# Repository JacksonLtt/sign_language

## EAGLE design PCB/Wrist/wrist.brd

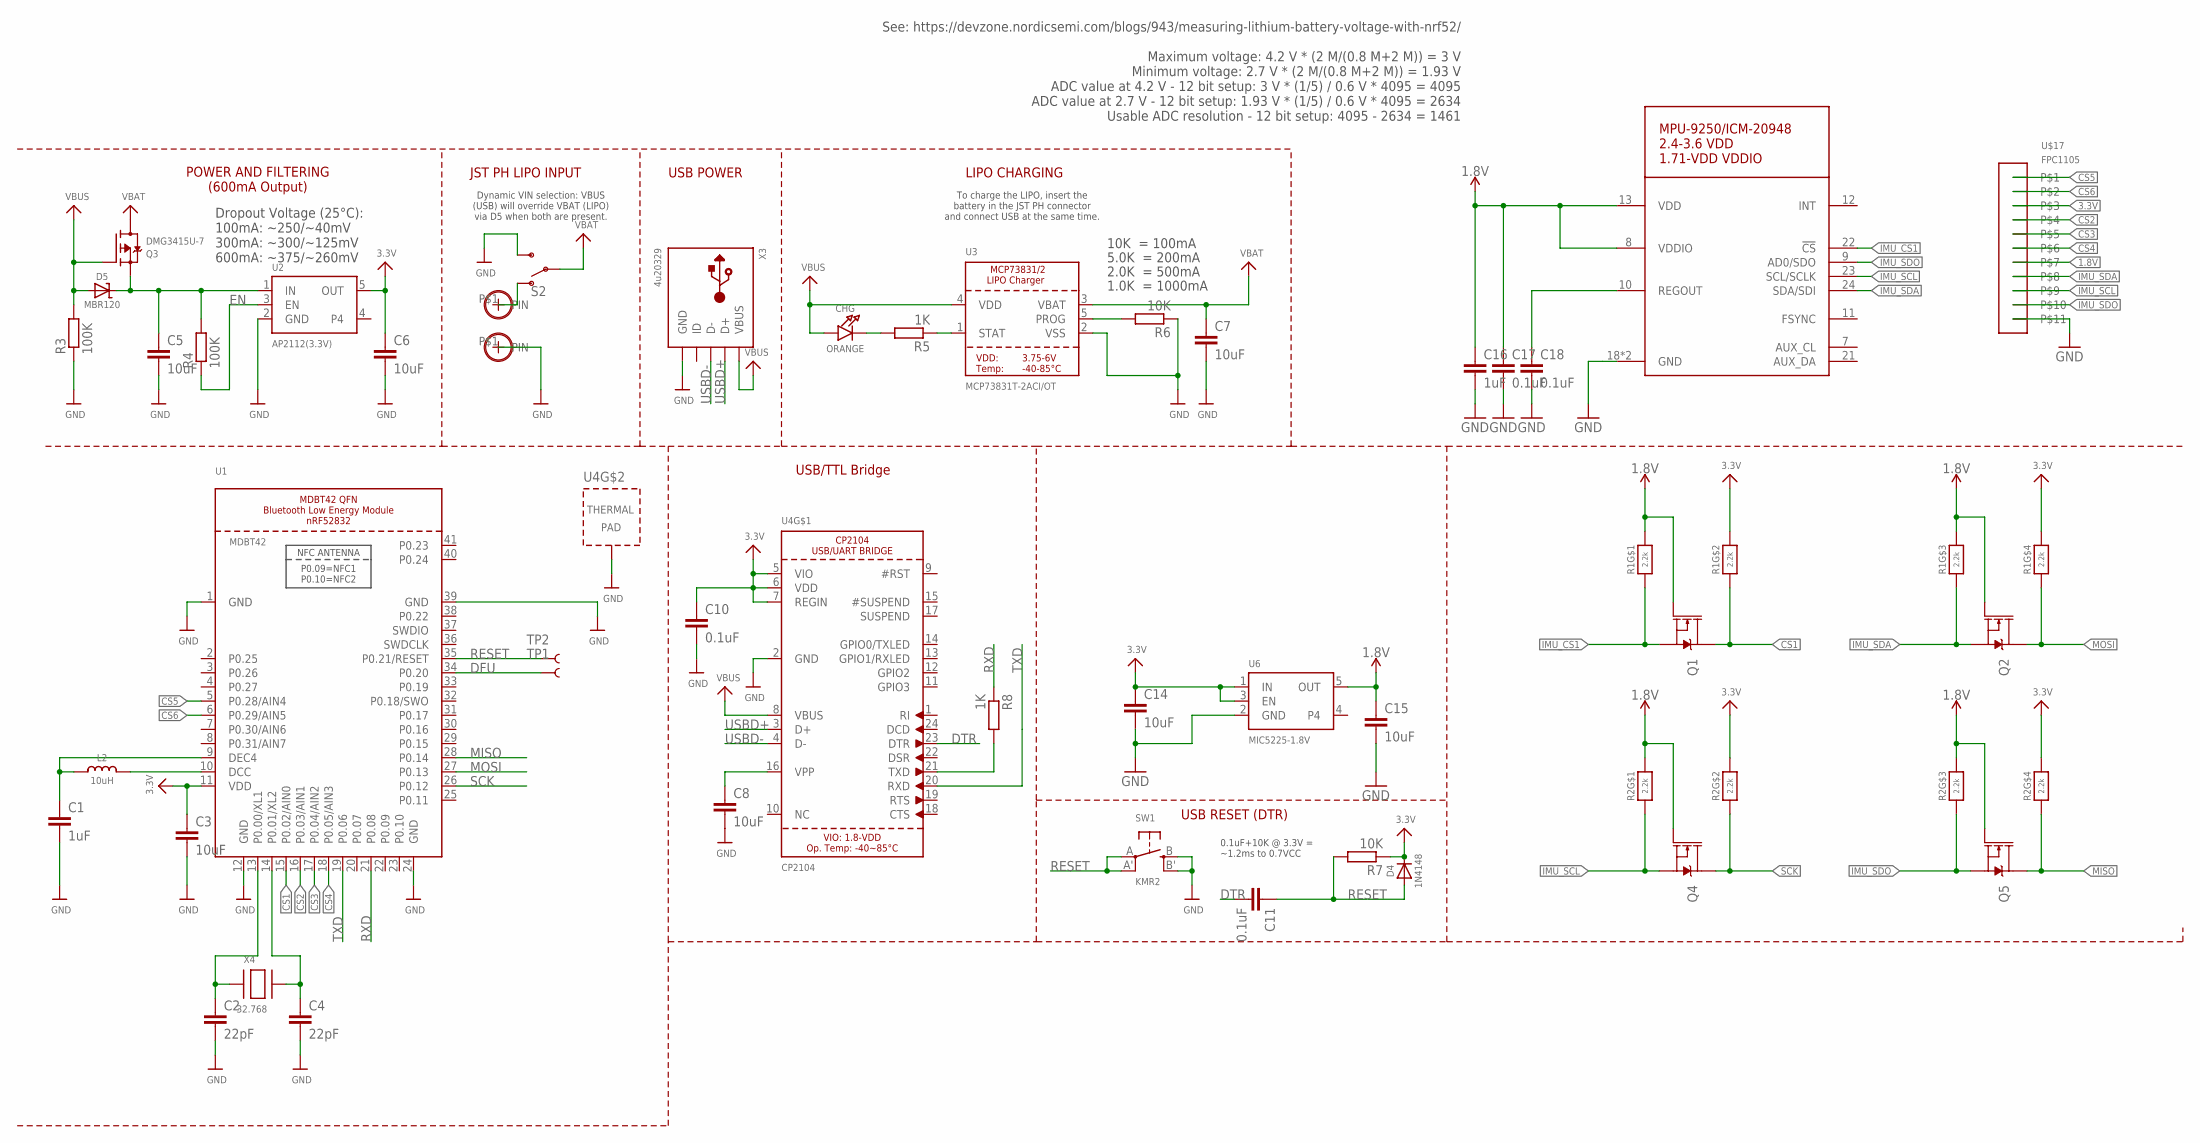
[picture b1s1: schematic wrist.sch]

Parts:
C1, C16: 1uF; SPARKFUN-CAPACITORS_0402
C2, C4: 22pF; SPARKFUN-CAPACITORS_0402
C3, C5, C6, C7, C8, C14, C15: 10uF; SPARKFUN-CAPACITORS_0402
C10, C11, C17, C18: 0.1uF; SPARKFUN-CAPACITORS_0402
CHG: ORANGE; CHIPLED_0805_NOOUTLINE
D4: 1N4148; SOD-323
D5: MBR120; SOD-123
IC1: ADAFRUIT_SENSOR_MPU-9250_ICM20948; ADAFRUIT_SENSOR_QFN24_3MM_NOEP
L2: 10uH; 0805-NO
Q1, Q2, Q4, Q5: 20V/0.2A/8MHz/1.2Ω/1Vth; SPARKFUN-DISCRETESEMI_SOT-416FL
Q3: DMG3415U-7; SOT23-R
R1, R2: 2.2k; MICROBUILDER_RESPACK_4X0603
R3, R4: 100K; R0603
R5, R8: 1K; R0603
R6, R7: 10K; R0603
S2: SWITCH-SPDT-SMD-RIGHT-ANGLE; SWITCH_SPST_SMD_A
SW1: KMR2; BTN_KMR2_4.6X2.8
TP1, TP2: TEST-POINT3; PAD.03X.03
U1: MDBT42; BLE_MODULE_RAYTAC_MDBT42
U2: AP2112(3.3V); SOT23-5
U3: MCP73831T-2ACI/OT; SOT23-5
U4: CP2104; QFN24_4MM_SMSC
U6: MIC5225-1.8V; MICROBUILDER_SOT23-5
U$17: FPC1105
U$23, U$28: M3-HOLE_M0.9-HOLE0.9MM; M3-HOLE_M0.9-HOLE
X3: 4u20329; 4UCONN_20329_V2
X4: 32.768; XTAL3215

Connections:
1.8V: C15.1, C16.1, C17.1, IC1.8 (VDDIO), IC1.13 (VDD), Q1.1 (G), Q2.1 (G), Q4.1 (G), Q5.1 (G), R1.6 (2), R1.8 (2), R2.6 (2), R2.8 (2), U6.5 (OUT), U$17.P$7
3.3V: C3.1, C6.1, C10.1, C14.1, D4.C, R1.5 (2), R1.7 (2), R2.5 (2), R2.7 (2), R7.1, U1.11 (VDD), U2.5 (OUT), U4.5 (VIO), U4.6 (VDD), U4.7 (REGIN), U6.1 (IN), U6.3 (EN), U$17.P$3
CS1: Q1.3 (D), R1.2 (1), U1.15 (P0.02/AIN0)
CS2: U1.16 (P0.03/AIN1), U$17.P$4
CS3: U1.17 (P0.04/AIN2), U$17.P$5
CS4: U1.18 (P0.05/AIN3), U$17.P$6
CS5: U1.5 (P0.28/AIN4), U$17.P$1
CS6: U1.6 (P0.29/AIN5), U$17.P$2
DFU: TP1.P$1, U1.34 (P0.20)
DTR: C11.2, U4.23 (DTR)
EN: R4.1, U2.3 (EN)
GND: C1.2, C2.2, C3.2, C4.2, C5.2, C6.2, C7.2, C8.2, C10.2, C14.2, C15.2, C16.2, C17.2, C18.2, IC1.18 (GND), IC1.20 (GND), R3.1, R6.1, S2.3 (S), SW1.B (S), SW1.B' (S1), U1.1 (GND), U1.12 (GND), U1.24 (GND), U1.39 (GND), U2.2 (GND), U3.2 (VSS), U4.2 (GND), U4.THERM (TP), U6.2 (GND), U$17.P$11, U$28.P$1, X3.BASE@1 (GND), X3.BASE@2 (GND), X3.GND, X3.SPRT@1 (GND), X3.SPRT@2 (GND), X3.SPRT@3 (GND), X3.SPRT@4 (GND)
IMU_CS1: IC1.22 (!CS), Q1.2 (S), R1.1
IMU_SCL: IC1.23 (SCL/SCLK), Q4.2 (S), R2.1, U$17.P$9
IMU_SDA: IC1.24 (SDA/SDI), Q2.2 (S), R1.3 (1), U$17.P$8
IMU_SDO: IC1.9 (AD0/SDO), Q5.2 (S), R2.3 (1), U$17.P$10
MISO: Q5.3 (D), R2.4 (1), U1.28 (P0.14)
MOSI: Q2.3 (D), R1.4 (1), U1.27 (P0.13)
unnamed: C2.1, U1.13 (P0.00/XL1), X4.P$1
unnamed: C4.1, U1.14 (P0.01/XL2), X4.P$2
unnamed: L2.2, U1.10 (DCC)
unnamed: CHG.C, R5.2
unnamed: S2.1 (O), U$23.P$1
unnamed: C18.1, IC1.10 (REGOUT)
unnamed: C1.1, L2.1, U1.9 (DEC4)
unnamed: R5.1, U3.1 (STAT)
unnamed: R6.2, U3.5 (PROG)
unnamed: R8.2, U4.21 (TXD)
unnamed: C8.1, U4.16 (VPP)
RESET: C11.1, D4.A, R7.2, SW1.A, SW1.A' (P1), TP2.P$1, U1.35 (P0.21/RESET)
RXD: R8.1, U1.21 (P0.08)
SCK: Q4.3 (D), R2.2 (1), U1.26 (P0.12)
TXD: U1.19 (P0.06), U4.20 (RXD)
USBD+: U4.3 (D+), X3.D+
USBD-: U4.4 (D-), X3.D-
VBAT: C7.1, Q3.3 (D), S2.2, U3.3 (VBAT)
VBUS: CHG.A, D5.A, Q3.1 (G), R3.2, U3.4 (VDD), U4.8 (VBUS), X3.VBUS
VIN: C5.1, D5.C, Q3.2 (S), R4.2, U2.1 (IN)

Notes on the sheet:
10K = 100mA
5.0K = 200mA
2.0K = 500mA
1.0K = 1000mA
LIPO CHARGING
To charge the LIPO, insert the battery in the JST PH connector and connect USB at the same time.
POWER AND FILTERING (600mA Output)
JST PH LIPO INPUT
Dynamic VIN selection: VBUS (USB) will override VBAT (LIPO) via D5 when both are present.
Dropout Voltage (25°C): 100mA: ~250/~40mV 300mA: ~300/~125mV 600mA: ~375/~260mV
USB POWER
USB/TTL Bridge
See: https://devzone.nordicsemi.com/blogs/943/measuring-lithium-battery-voltage-with-nrf52/ Maximum voltage: 4.2 V * (2 M/(0.8 M+2 M)) = 3 V Minimum voltage: 2.7 V * (2 M/(0.8 M+2 M)) = 1.93 V ADC value at 4.2 V - 12 bit setup: 3 V * (1/5) / 0.6 V * 4095 = 4095 ADC value at 2.7 V - 12 bit setup: 1.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
USB RESET (DTR)
0.1uF+10K @ 3.3V = ~1.2ms to 0.7VCC

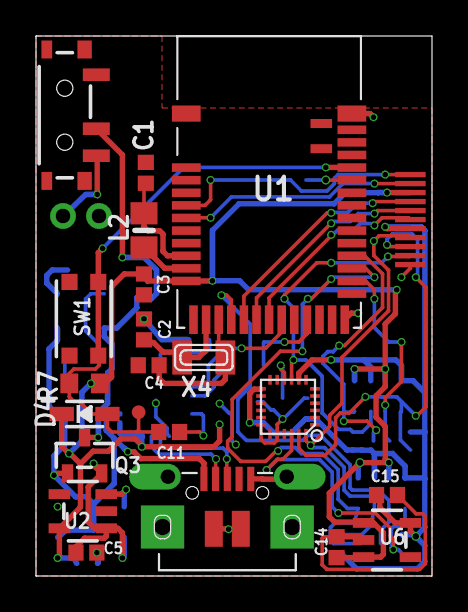
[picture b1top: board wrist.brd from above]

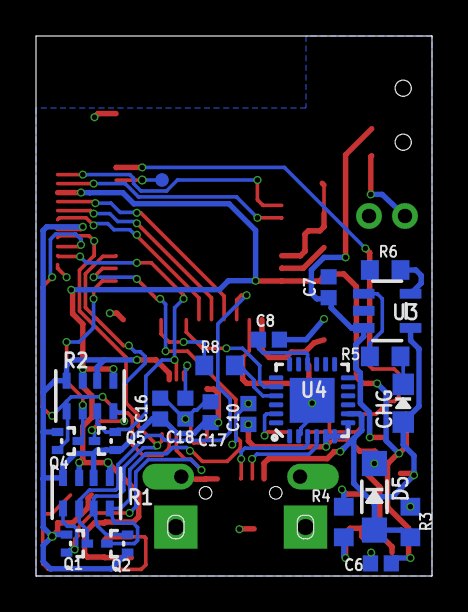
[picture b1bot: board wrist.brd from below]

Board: 2 copper layers, 22.0 x 30.0 mm, 47 parts (23 on the bottom side), 38 nets.

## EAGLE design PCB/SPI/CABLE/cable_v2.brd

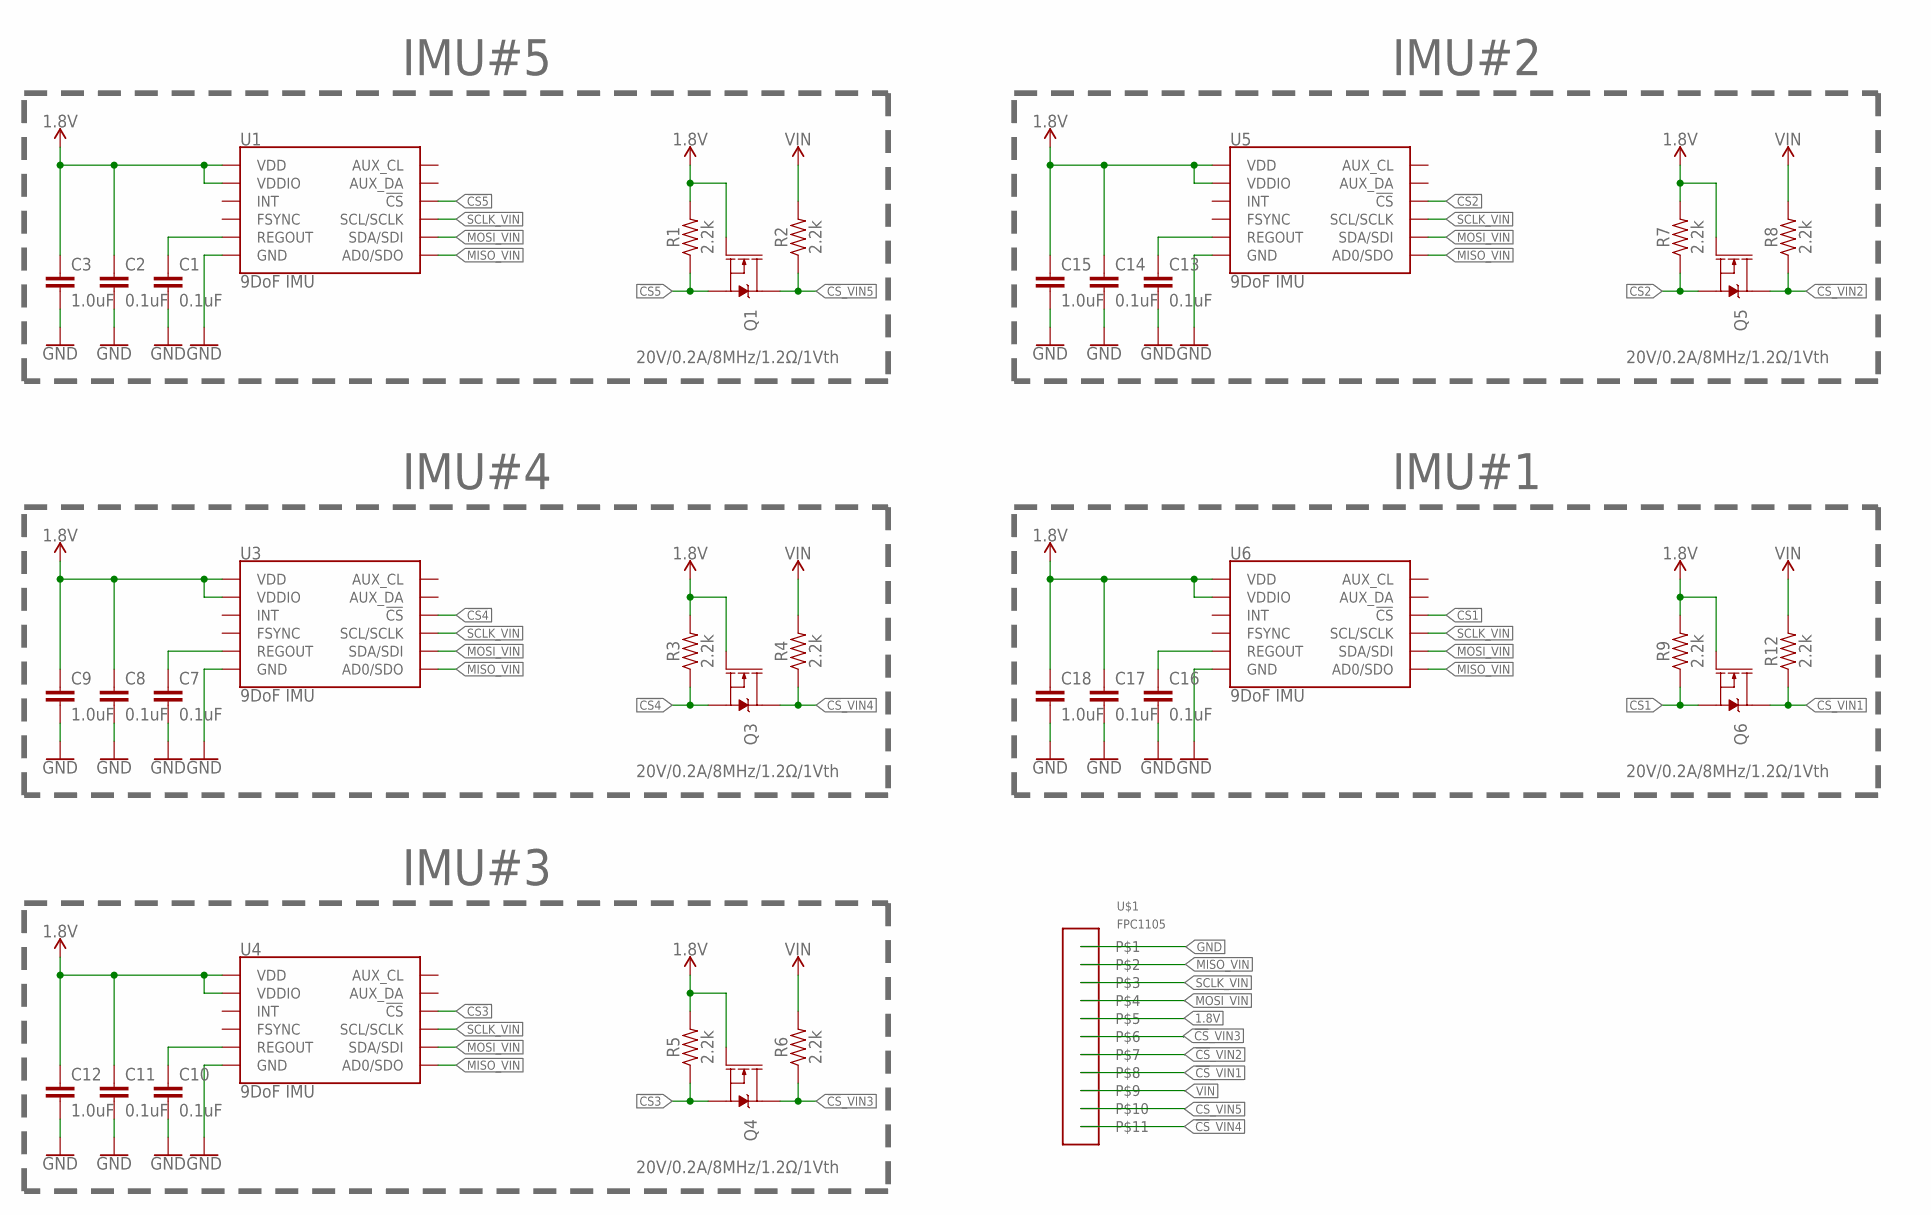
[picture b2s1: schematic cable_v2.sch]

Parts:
C1, C2, C7, C8, C10, C11, C13, C14, C16, C17: 0.1uF; C0402
C3, C9, C12, C15, C18: 1.0uF; C0402
Q1, Q3, Q4, Q5, Q6: 20V/0.2A/8MHz/1.2Ω/1Vth; SOT-416FL
R1, R2, R3, R4, R5, R6, R7, R8, R9, R12: 2.2k; 0402-TIGHT
U1, U3, U4, U5, U6: 9DoF IMU; QFN24-3X3
U$1: FPC1105

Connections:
1.8V: C2.1, C3.1, C8.1, C9.1, C11.1, C12.1, C14.1, C15.1, C17.1, C18.1, Q1.1 (G), Q3.1 (G), Q4.1 (G), Q5.1 (G), Q6.1 (G), R1.2, R3.2, R5.2, R7.2, R9.2, U1.8 (VDDIO), U1.13 (VDD), U3.8 (VDDIO), U3.13 (VDD), U4.8 (VDDIO), U4.13 (VDD), U5.8 (VDDIO), U5.13 (VDD), U6.8 (VDDIO), U6.13 (VDD), U$1.P$5
!CS1: Q6.2 (S), R9.1, U6.22 (!CS)
!CS2: Q5.2 (S), R7.1, U5.22 (!CS)
!CS3: Q4.2 (S), R5.1, U4.22 (!CS)
!CS4: Q3.2 (S), R3.1, U3.22 (!CS)
!CS5: Q1.2 (S), R1.1, U1.22 (!CS)
!CS!_VIN1: Q6.3 (D), R12.1, U$1.P$8
!CS!_VIN2: Q5.3 (D), R8.1, U$1.P$7
!CS!_VIN3: Q4.3 (D), R6.1, U$1.P$6
!CS!_VIN4: Q3.3 (D), R4.1, U$1.P$11
!CS!_VIN5: Q1.3 (D), R2.1, U$1.P$10
GND: C1.2, C2.2, C3.2, C7.2, C8.2, C9.2, C10.2, C11.2, C12.2, C13.2, C14.2, C15.2, C16.2, C17.2, C18.2, U1.18 (GND), U1.20 (GND), U3.18 (GND), U3.20 (GND), U4.18 (GND), U4.20 (GND), U5.18 (GND), U5.20 (GND), U6.18 (GND), U6.20 (GND), U$1.P$1
MISO_VIN: U1.9 (AD0/SDO), U3.9 (AD0/SDO), U4.9 (AD0/SDO), U5.9 (AD0/SDO), U6.9 (AD0/SDO), U$1.P$2
MOSI_VIN: U1.24 (SDA/SDI), U3.24 (SDA/SDI), U4.24 (SDA/SDI), U5.24 (SDA/SDI), U6.24 (SDA/SDI), U$1.P$4
unnamed: C1.1, U1.10 (REGOUT)
unnamed: C7.1, U3.10 (REGOUT)
unnamed: C10.1, U4.10 (REGOUT)
unnamed: C13.1, U5.10 (REGOUT)
unnamed: C16.1, U6.10 (REGOUT)
SCLK_VIN: U1.23 (SCL/SCLK), U3.23 (SCL/SCLK), U4.23 (SCL/SCLK), U5.23 (SCL/SCLK), U6.23 (SCL/SCLK), U$1.P$3
VIN: R2.2, R4.2, R6.2, R8.2, R12.2, U$1.P$9

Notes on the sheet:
IMU#5
IMU#4
IMU#3
IMU#2
IMU#1

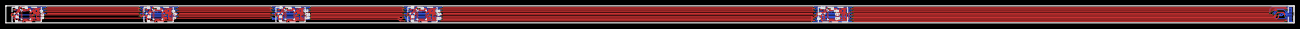
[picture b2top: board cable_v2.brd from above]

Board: 2 copper layers, 439.4 x 5.8 mm, 36 parts (1 on the bottom side), 21 nets.

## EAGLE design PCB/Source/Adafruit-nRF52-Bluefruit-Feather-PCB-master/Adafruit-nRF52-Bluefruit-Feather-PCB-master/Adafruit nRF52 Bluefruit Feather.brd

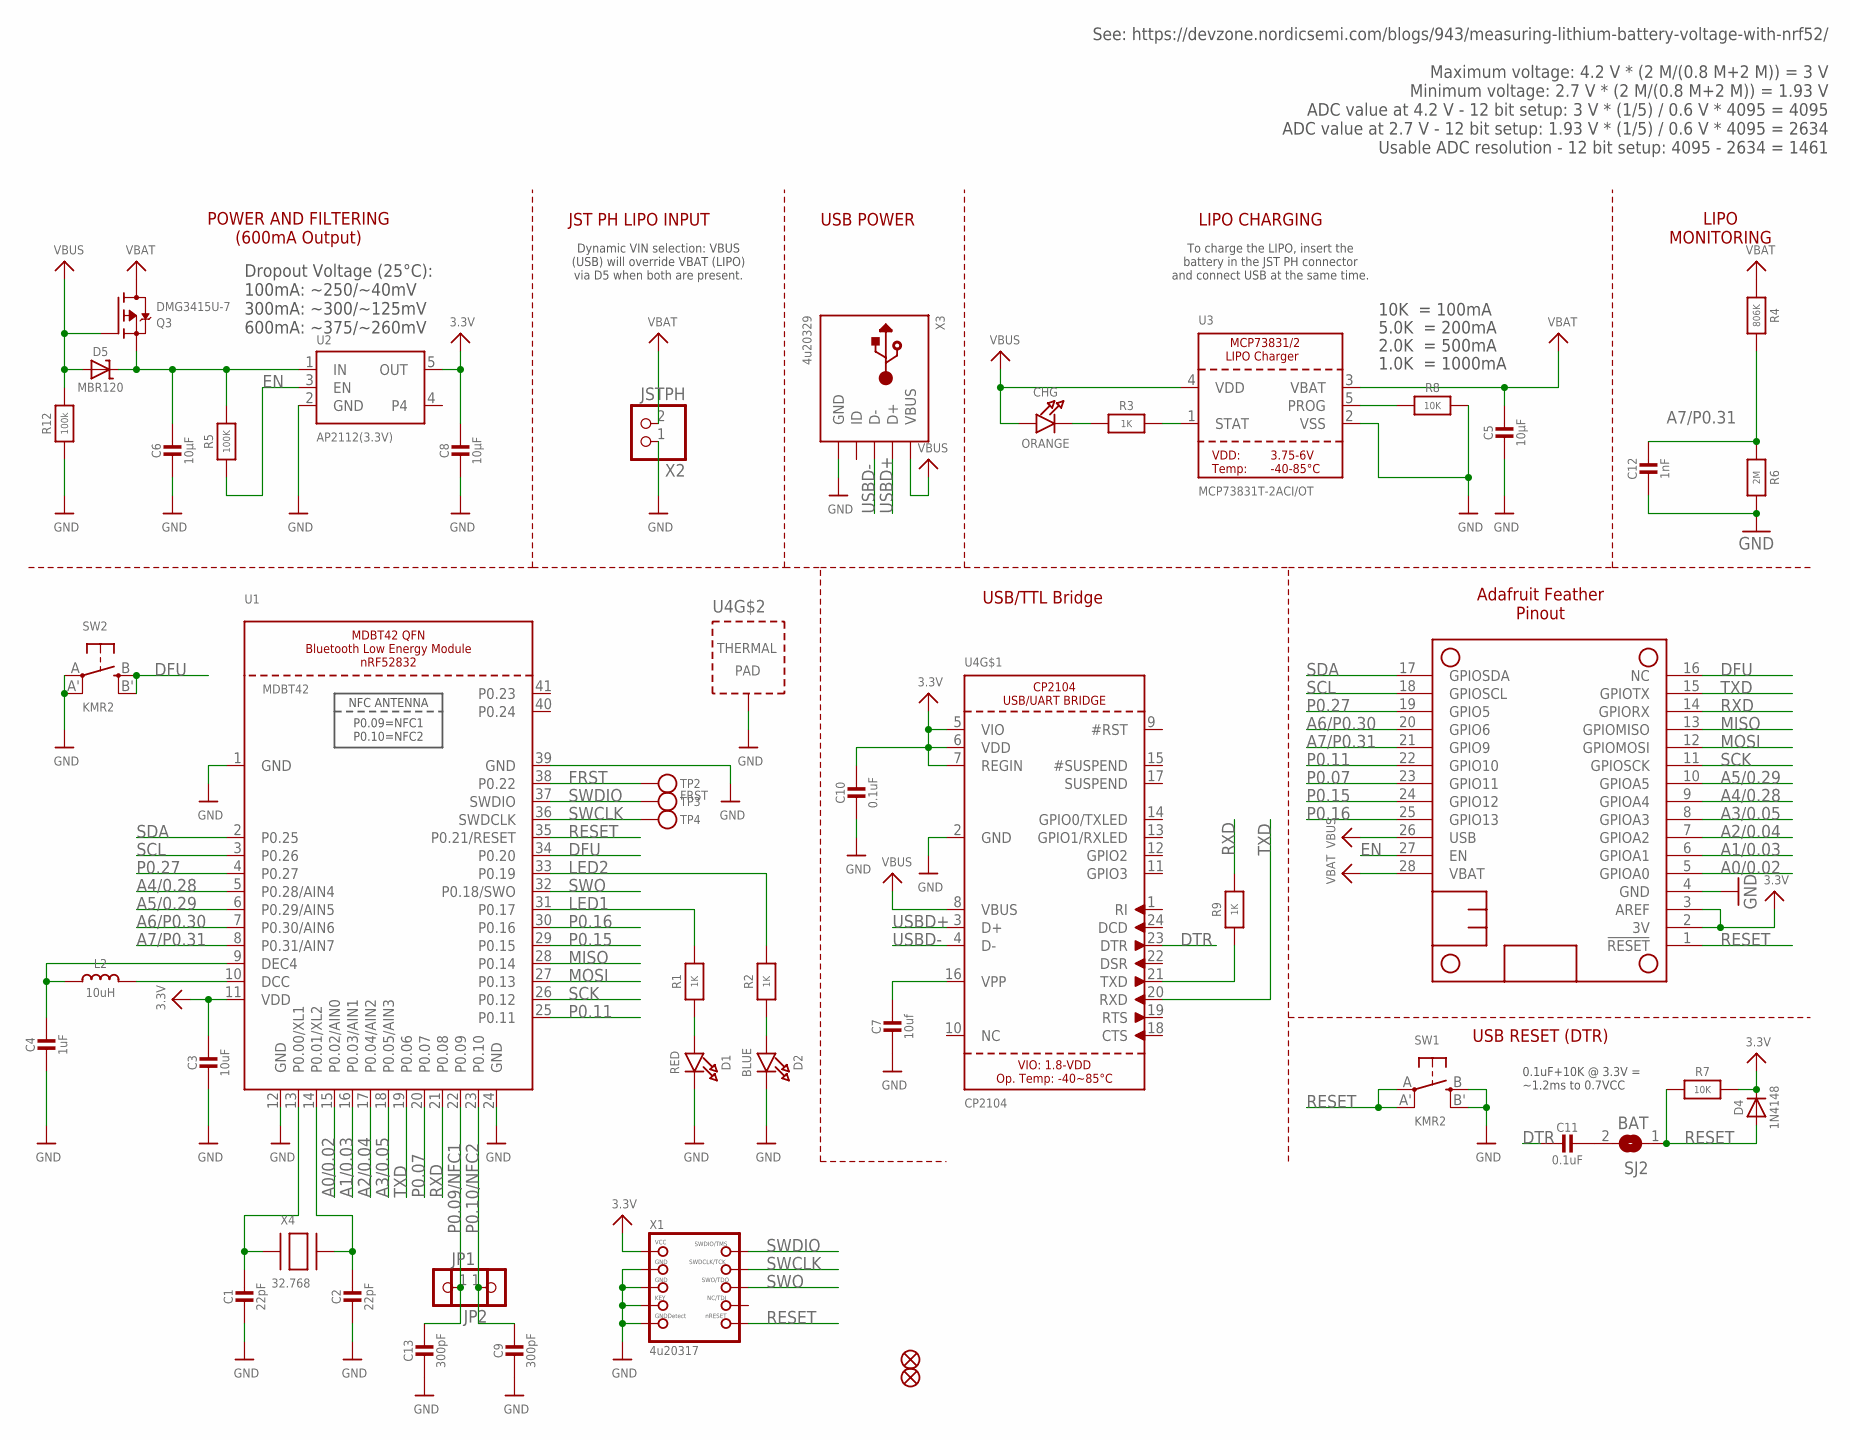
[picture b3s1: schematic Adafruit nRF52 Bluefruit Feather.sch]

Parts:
C1, C2: 22pF; 0603-NO
C3: 10uF; 0805-NO
C4: 1uF; 0603-NO
C5, C6, C8: 10µF; 0805-NO
C7: 10uf; 0805-NO
C9, C13: 300pF; _0603MP
C10, C11: 0.1uF; 0603-NO
C12: 1nF; 0603-NO
CHG: ORANGE; CHIPLED_0805_NOOUTLINE
D1: RED; CHIPLED_0805_NOOUTLINE
D2: BLUE; CHIPLED_0805_NOOUTLINE
D4: 1N4148; SOD-323
D5: MBR120; SOD-123
FID1, FID3: FIDUCIAL_1MM
JP1, JP2: HEADER-1X12MM; 1X01_2MM
L2: 10uH; 0805-NO
MS1: FEATHERWING_NODIM
Q3: DMG3415U-7; SOT23-R
R1, R2, R3, R9: 1K; 0603-NO
R4: 806K; 0603-NO
R5: 100K; 0603-NO
R6: 2M; 0603-NO
R7, R8: 10K; 0603-NO
R12: 100k; 0603-NO
SJ2: BAT; SOLDERJUMPER_CLOSEDWIRE
SW1, SW2: KMR2; BTN_KMR2_4.6X2.8
TP2: FRST; PAD-1.5X2.0
TP3, TP4: TESTPOINTROUND2MM; TESTPOINT_ROUND_2MM
U1: MDBT42; BLE_MODULE_RAYTAC_MDBT42
U2: AP2112(3.3V); SOT23-5
U3: MCP73831T-2ACI/OT; SOT23-5
U4: CP2104; QFN24_4MM_SMSC
X1: 4u20317; 2X05_1.27MM_BOX_POSTS
X2: JSTPH; JSTPH2
X3: 4u20329; 4UCONN_20329_V2
X4: 32.768; XTAL3215

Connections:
3.3V: C3.1, C8.1, C10.1, D4.C, MS1.2 (3V), MS1.3 (AREF), R7.2, U1.11 (VDD), U2.5 (OUT), U4.5 (VIO), U4.6 (VDD), U4.7 (REGIN), X1.1 (VCC)
A0/0.02: MS1.5 (GPIOA0), U1.15 (P0.02/AIN0)
A1/0.03: MS1.6 (GPIOA1), U1.16 (P0.03/AIN1)
A2/0.04: MS1.7 (GPIOA2), U1.17 (P0.04/AIN2)
A3/0.05: MS1.8 (GPIOA3), U1.18 (P0.05/AIN3)
A4/0.28: MS1.9 (GPIOA4), U1.5 (P0.28/AIN4)
A5/0.29: MS1.10 (GPIOA5), U1.6 (P0.29/AIN5)
A6/P0.30: MS1.20 (GPIO6), U1.7 (P0.30/AIN6)
A7/P0.31: C12.1, MS1.21 (GPIO9), R4.2, R6.1, U1.8 (P0.31/AIN7)
DFU: MS1.16 (NC), SW2.B (S), SW2.B' (S1), U1.34 (P0.20)
DTR: C11.2, U4.23 (DTR)
EN: MS1.27 (EN), R5.1, U2.3 (EN)
FRST: TP2.P$1, U1.38 (P0.22)
GND: C1.2, C2.2, C3.2, C4.2, C5.2, C6.2, C7.2, C8.2, C9.2, C10.2, C12.2, C13.2, D1.C, D2.C, MS1.4 (GND), R6.2, R8.2, R12.1, SW1.B (S), SW1.B' (S1), SW2.A, SW2.A' (P1), U1.1 (GND), U1.12 (GND), U1.24 (GND), U1.39 (GND), U2.2 (GND), U3.2 (VSS), U4.2 (GND), U4.THERM (TP), X1.3 (GND), X1.5 (GND), X1.7 (KEY), X1.9 (GNDDETECT), X2.1, X3.BASE@1 (GND), X3.BASE@2 (GND), X3.GND, X3.SPRT@1 (GND), X3.SPRT@2 (GND), X3.SPRT@3 (GND), X3.SPRT@4 (GND)
LED1: R1.2, U1.31 (P0.17)
LED2: R2.2, U1.33 (P0.19)
MISO: MS1.13 (GPIOMISO), U1.28 (P0.14)
MOSI: MS1.12 (GPIOMOSI), U1.27 (P0.13)
unnamed: C1.1, U1.13 (P0.00/XL1), X4.P$1
unnamed: C2.1, U1.14 (P0.01/XL2), X4.P$2
unnamed: L2.2, U1.10 (DCC)
unnamed: CHG.C, R3.1
unnamed: D1.A, R1.1
unnamed: D2.A, R2.1
unnamed: C4.1, L2.1, U1.9 (DEC4)
unnamed: R3.2, U3.1 (STAT)
unnamed: R8.1, U3.5 (PROG)
unnamed: R9.1, U4.21 (TXD)
unnamed: C11.1, SJ2.2
unnamed: C7.1, U4.16 (VPP)
P0.07: MS1.23 (GPIO11), U1.20 (P0.07)
P0.09/NFC1: C13.1, JP2.1, U1.22 (P0.09)
P0.10/NFC2: C9.1, JP1.1, U1.23 (P0.10)
P0.11: MS1.22 (GPIO10), U1.25 (P0.11)
P0.15: MS1.24 (GPIO12), U1.29 (P0.15)
P0.16: MS1.25 (GPIO13), U1.30 (P0.16)
P0.27: MS1.19 (GPIO5), U1.4 (P0.27)
RESET: D4.A, MS1.1 (!RESET), R7.1, SJ2.1, SW1.A, SW1.A' (P1), U1.35 (P0.21/RESET), X1.10 (NRESET)
RXD: MS1.14 (GPIORX), R9.2, U1.21 (P0.08)
SCK: MS1.11 (GPIOSCK), U1.26 (P0.12)
SCL: MS1.18 (GPIOSCL), U1.3 (P0.26)
SDA: MS1.17 (GPIOSDA), U1.2 (P0.25)
SWCLK: TP4.P$1, U1.36 (SWDCLK), X1.4 (SWDCLK)
SWDIO: TP3.P$1, U1.37 (SWDIO), X1.2 (SWDIO)
SWO: U1.32 (P0.18/SWO), X1.6 (SWO)
TXD: MS1.15 (GPIOTX), U1.19 (P0.06), U4.20 (RXD)
USBD+: U4.3 (D+), X3.D+
USBD-: U4.4 (D-), X3.D-
VBAT: C5.1, MS1.28 (VBAT), Q3.3 (D), R4.1, U3.3 (VBAT), X2.2
VBUS: CHG.A, D5.A, MS1.26 (USB), Q3.1 (G), R12.2, U3.4 (VDD), U4.8 (VBUS), X3.VBUS
VIN: C6.1, D5.C, Q3.2 (S), R5.2, U2.1 (IN)

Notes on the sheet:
10K = 100mA
5.0K = 200mA
2.0K = 500mA
1.0K = 1000mA
LIPO CHARGING
LIPO MONITORING
To charge the LIPO, insert the battery in the JST PH connector and connect USB at the same time.
POWER AND FILTERING (600mA Output)
JST PH LIPO INPUT
Dynamic VIN selection: VBUS (USB) will override VBAT (LIPO) via D5 when both are present.
Dropout Voltage (25°C): 100mA: ~250/~40mV 300mA: ~300/~125mV 600mA: ~375/~260mV
USB POWER
USB/TTL Bridge
Adafruit Feather Pinout
See: https://devzone.nordicsemi.com/blogs/943/measuring-lithium-battery-voltage-with-nrf52/ Maximum voltage: 4.2 V * (2 M/(0.8 M+2 M)) = 3 V Minimum voltage: 2.7 V * (2 M/(0.8 M+2 M)) = 1.93 V ADC value at 4.2 V - 12 bit setup: 3 V * (1/5) / 0.6 V * 4095 = 4095 ADC value at 2.7 V - 12 bit setup: 1.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
USB RESET (DTR)
0.1uF+10K @ 3.3V = ~1.2ms to 0.7VCC

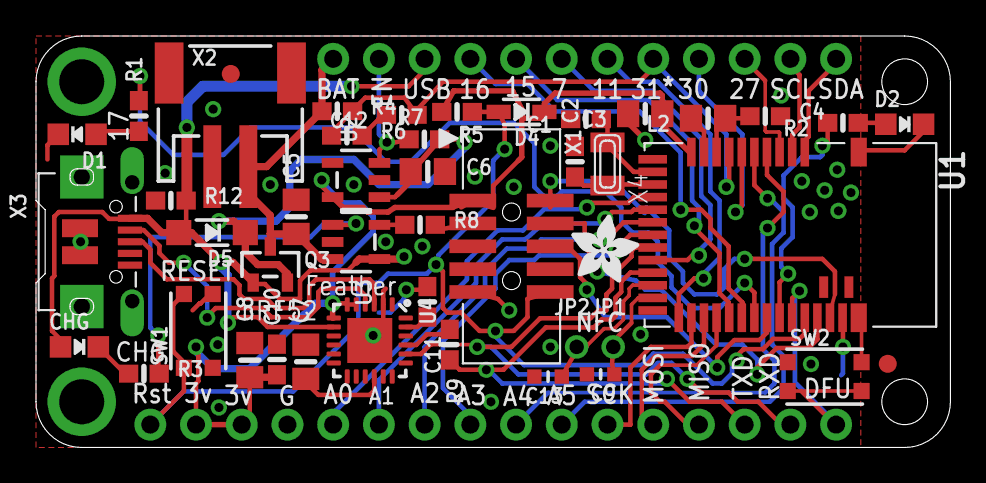
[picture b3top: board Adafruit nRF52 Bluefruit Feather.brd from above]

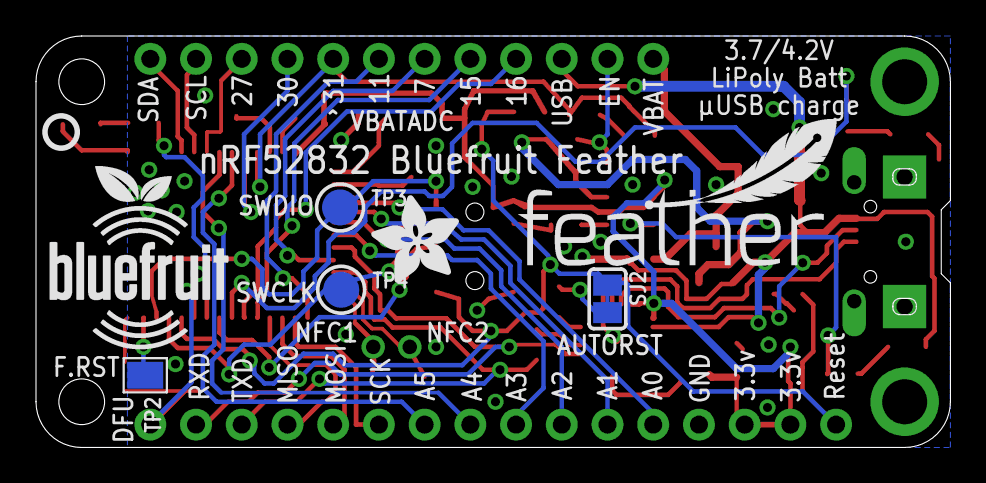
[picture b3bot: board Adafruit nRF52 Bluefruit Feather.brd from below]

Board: 2 copper layers, 50.8 x 22.9 mm, 54 parts (8 on the bottom side), 51 nets.

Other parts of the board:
U$17: PCBFEAT-REV-040
U$45: BLUEFRUITLOGO_100MM
U$46: FEATHERLOGO_MED
U$47: ADAFRUIT_5MM
U$49: ADAFRUIT_3.5MM

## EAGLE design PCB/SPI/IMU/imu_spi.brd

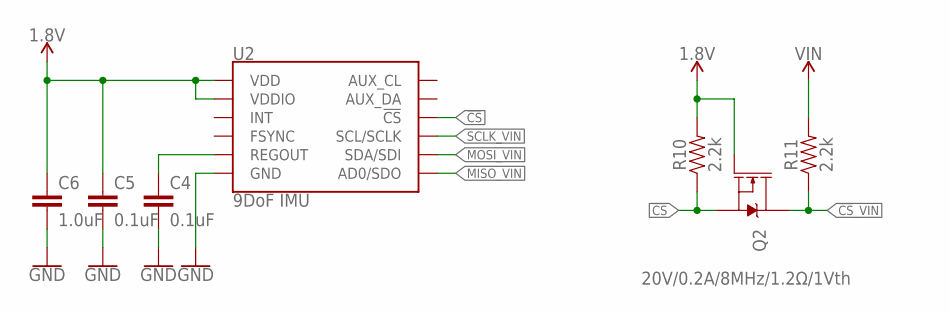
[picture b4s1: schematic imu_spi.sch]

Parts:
C4, C5: 0.1uF; C0402
C6: 1.0uF; C0402
Q2: 20V/0.2A/8MHz/1.2Ω/1Vth; SOT-416FL
R10, R11: 2.2k; 0402-TIGHT
U2: 9DoF IMU; QFN24-3X3

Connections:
1.8V: C5.1, C6.1, Q2.1 (G), R10.2, U2.8 (VDDIO), U2.13 (VDD)
!CS: Q2.2 (S), R10.1, U2.22 (!CS)
!CS!_VIN: Q2.3 (D), R11.1
GND: C4.2, C5.2, C6.2, U2.18 (GND), U2.20 (GND)
MISO_VIN: U2.9 (AD0/SDO)
MOSI_VIN: U2.24 (SDA/SDI)
unnamed: C4.1, U2.10 (REGOUT)
SCLK_VIN: U2.23 (SCL/SCLK)
VIN: R11.2

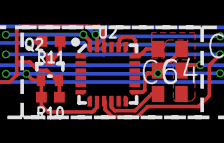
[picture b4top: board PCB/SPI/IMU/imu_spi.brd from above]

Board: 2 copper layers, 7 parts (0 on the bottom side), 5 nets.

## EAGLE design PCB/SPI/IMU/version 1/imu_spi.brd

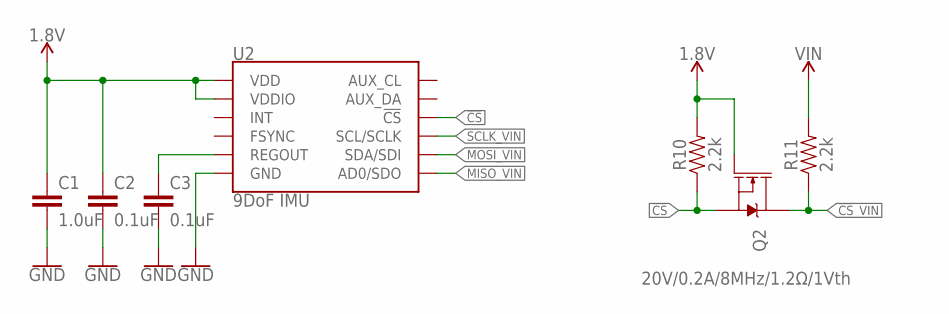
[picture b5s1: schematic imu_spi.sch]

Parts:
C1: 1.0uF; 0603
C2, C3: 0.1uF; 0603
Q2: 20V/0.2A/8MHz/1.2Ω/1Vth; SOT-416FL
R10, R11: 2.2k; 0402-TIGHT
U2: 9DoF IMU; QFN24-3X3

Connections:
1.8V: C1.1, C2.1, Q2.1 (G), R10.2, U2.8 (VDDIO), U2.13 (VDD)
!CS: Q2.2 (S), R10.1, U2.22 (!CS)
!CS!_VIN: Q2.3 (D), R11.1
GND: C1.2, C2.2, C3.2, U2.18 (GND), U2.20 (GND)
MISO_VIN: U2.9 (AD0/SDO)
MOSI_VIN: U2.24 (SDA/SDI)
unnamed: C3.1, U2.10 (REGOUT)
SCLK_VIN: U2.23 (SCL/SCLK)
VIN: R11.2

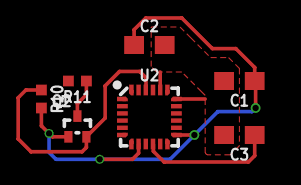
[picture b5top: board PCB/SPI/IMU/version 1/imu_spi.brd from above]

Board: 2 copper layers, 7 parts (0 on the bottom side), 5 nets.

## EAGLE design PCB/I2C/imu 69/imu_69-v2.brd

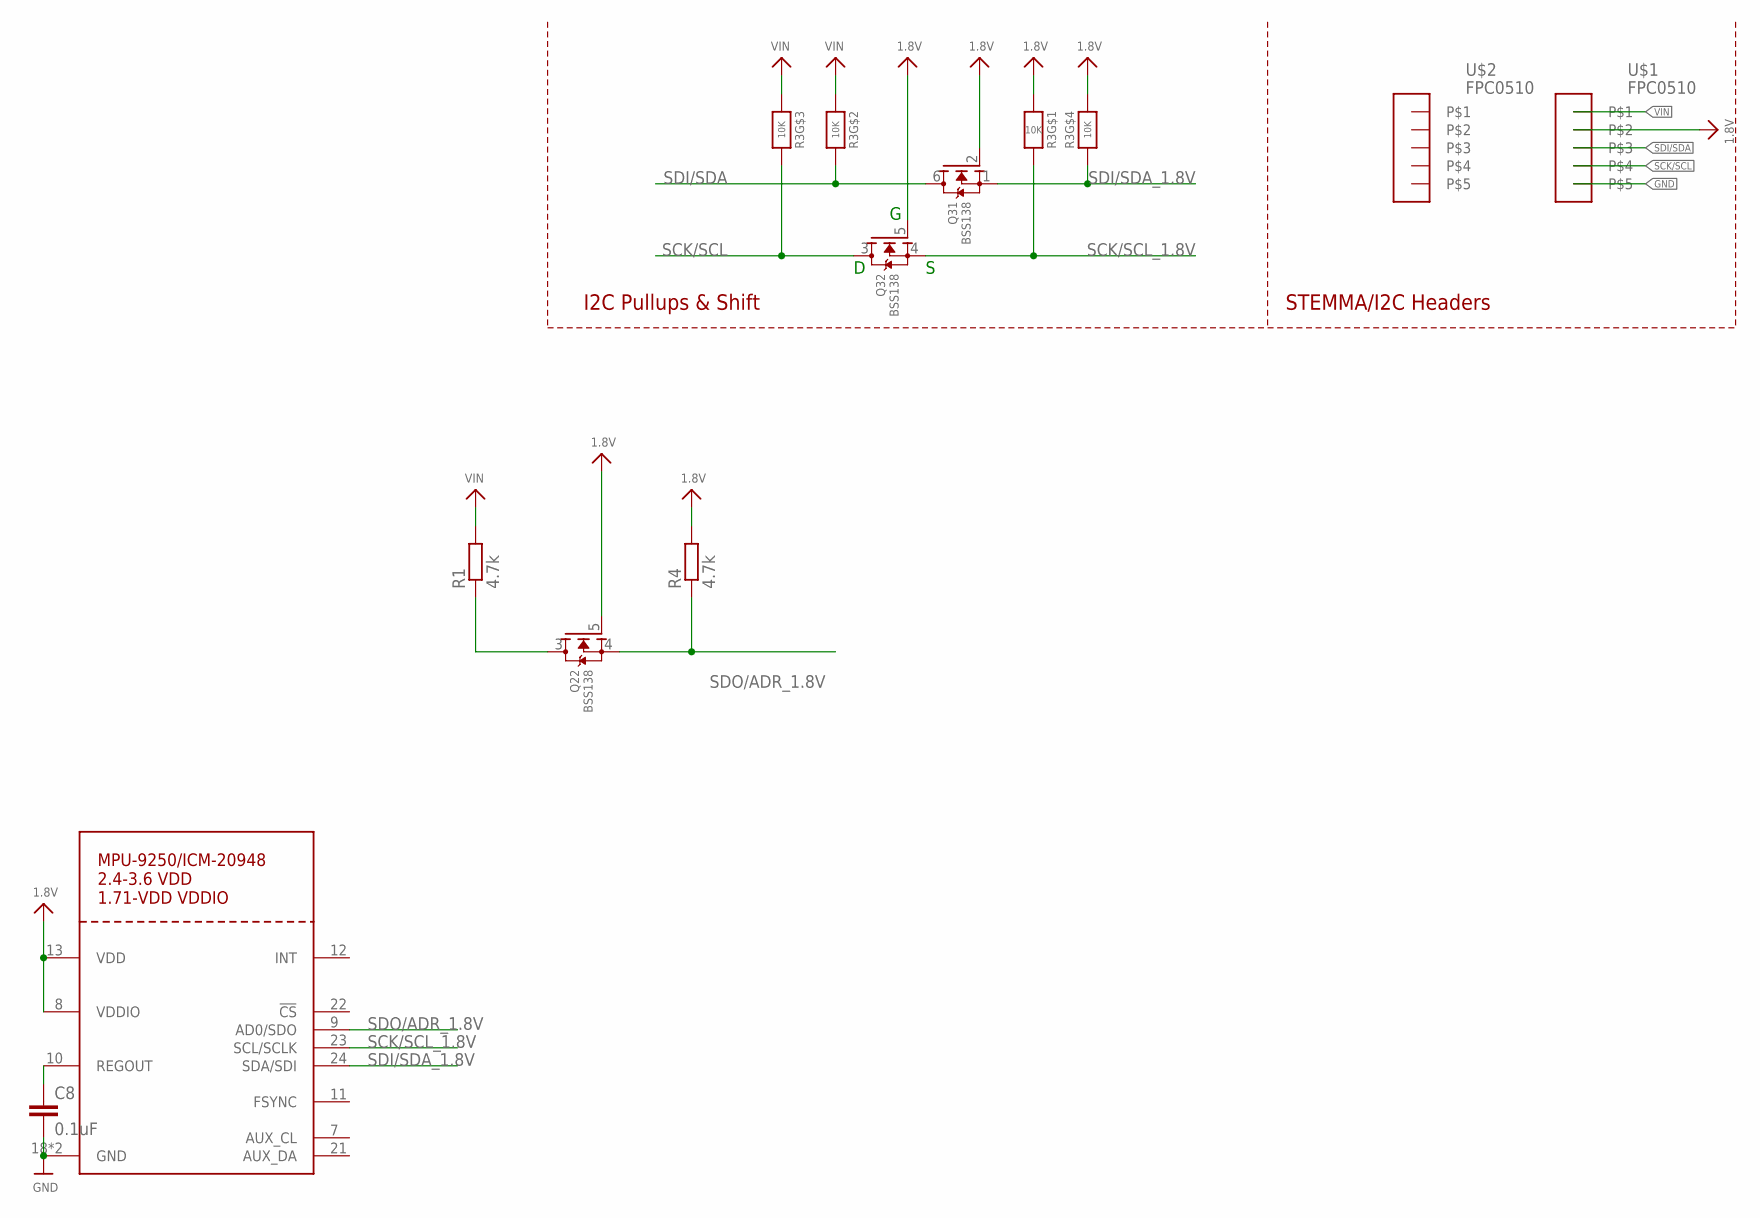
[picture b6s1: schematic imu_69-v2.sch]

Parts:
C8: 0.1uF; C0201
Q2, Q3: BSS138; SOT363
R1, R4: 4.7k; R0402
R3: 10K; RESPACK_4X0603
U$1, U$2: FPC0510
U$21: MPU-9250_ICM20948; QFN24_3MM_NOEP

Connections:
1.8V: Q2.5 (G), Q3.2 (G), Q3.5 (G), R3.4 (1), R3.8 (2), R4.2, U$1.P$2, U$21.8 (VDDIO), U$21.13 (VDD)
GND: C8.2, U$1.P$5, U$21.18 (GND), U$21.20 (GND)
REGOUT: C8.1, U$21.10 (REGOUT)
SCK/SCL: Q3.3 (D), R3.6 (2), U$1.P$4
SCK/SCL_1.8V: Q3.4 (S), R3.1, U$21.23 (SCL/SCLK)
SDI/SDA: Q3.6 (D), R3.7 (2), U$1.P$3
SDI/SDA_1.8V: Q3.1 (S), R3.5 (2), U$21.24 (SDA/SDI)
SDO/ADR: Q2.3 (D), R1.1
SDO/ADR_1.8V: Q2.4 (S), R4.1, U$21.9 (AD0/SDO)
VIN: R1.2, R3.2 (1), R3.3 (1), U$1.P$1

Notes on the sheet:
I2C Pullups & Shift
STEMMA/I2C Headers

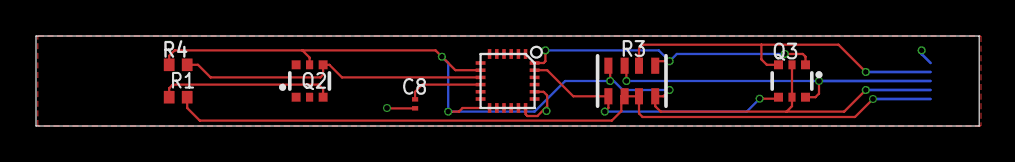
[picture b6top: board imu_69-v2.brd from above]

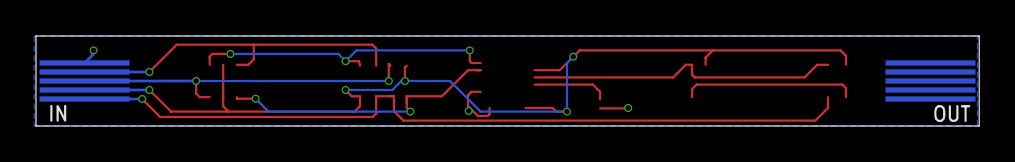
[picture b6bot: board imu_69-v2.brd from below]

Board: 2 copper layers, 52.4 x 5.0 mm, 9 parts (2 on the bottom side), 10 nets.

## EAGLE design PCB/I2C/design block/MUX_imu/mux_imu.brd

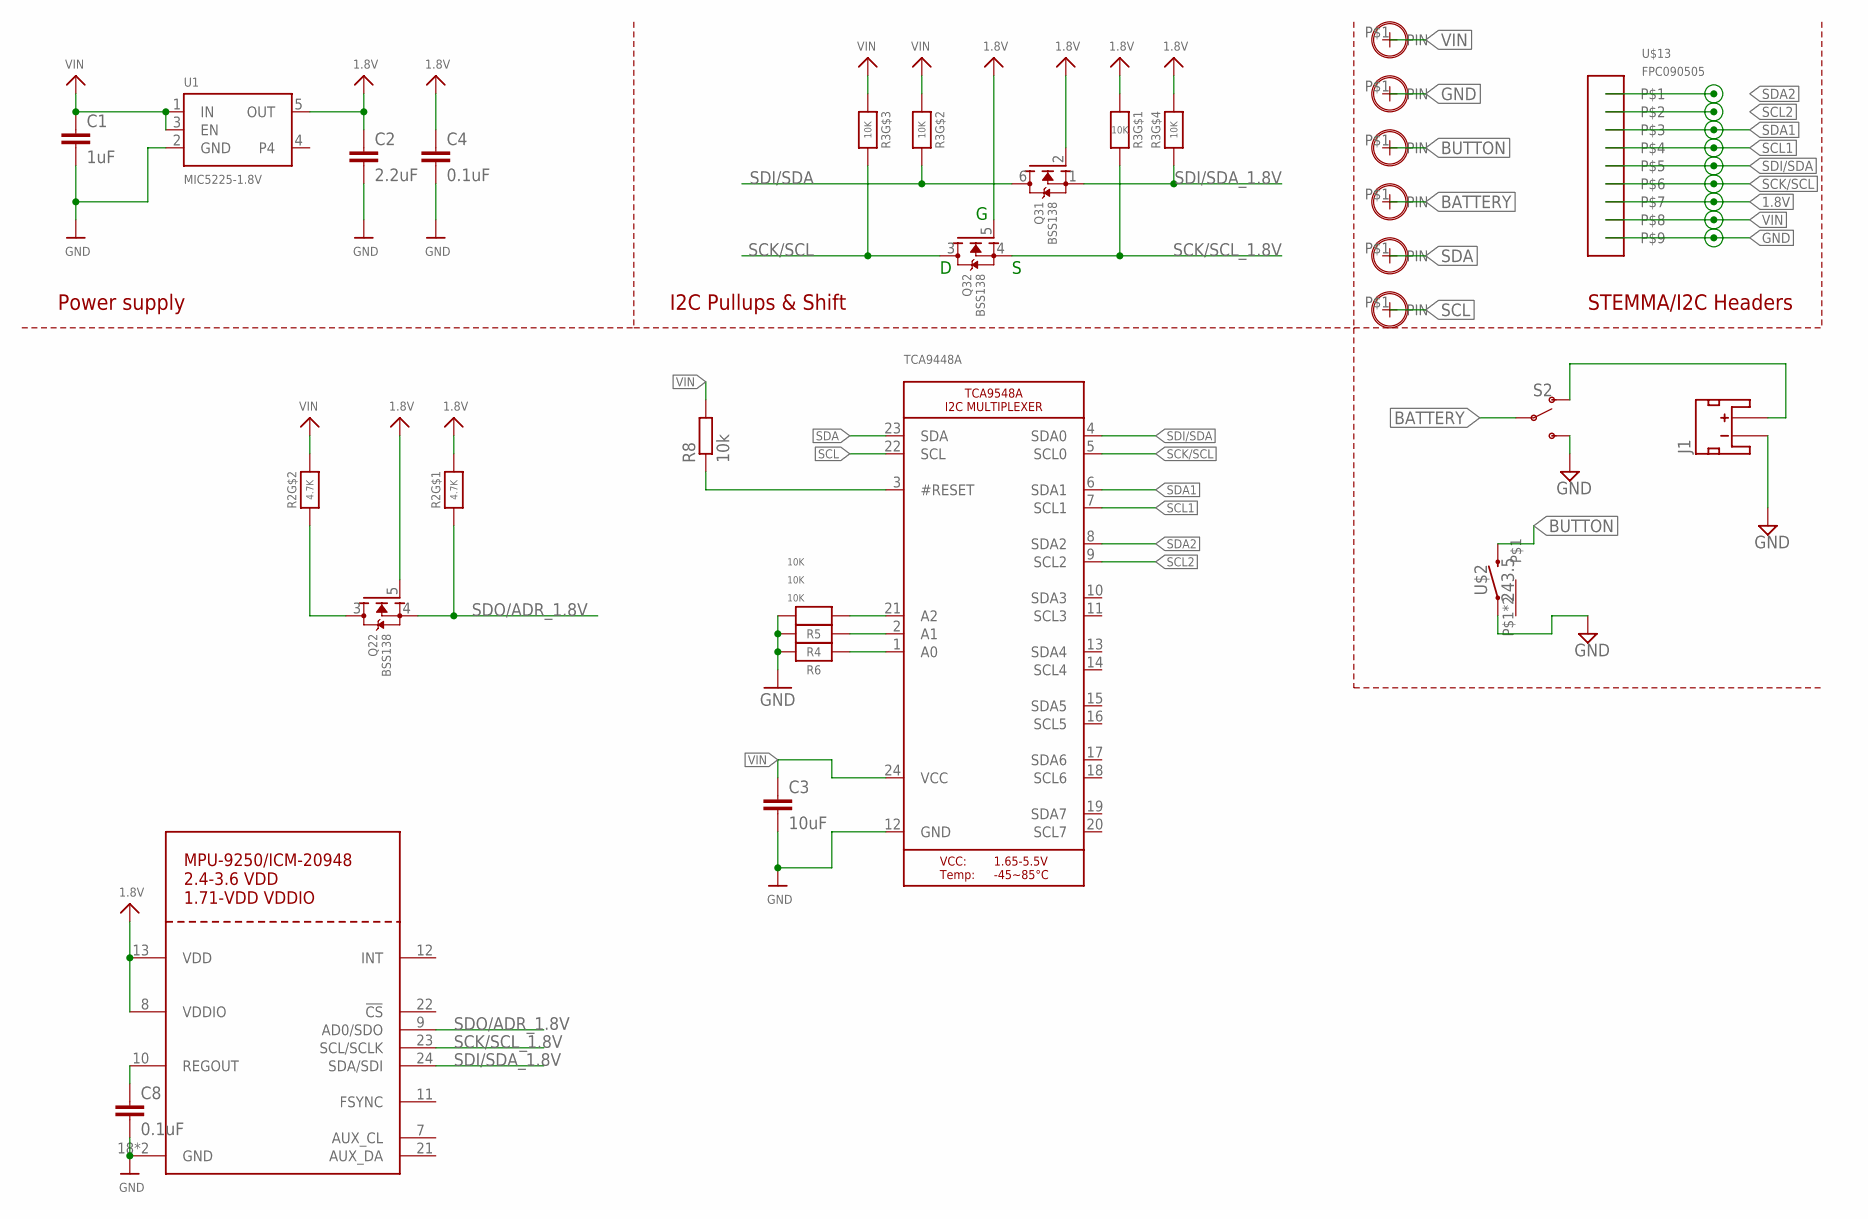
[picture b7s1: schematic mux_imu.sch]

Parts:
C1: 1uF; C0402
C2: 2.2uF; C0402
C3: 10uF; C0402
C4, C8: 0.1uF; C0402
J1: JST_2MM_MALE; JST-2-SMD
Q2, Q3: BSS138; SOT363
R2: 4.7K; RESPACK_4X0603
R3: 10K; RESPACK_4X0603
R4, R5, R6: 10K; 0805-NO
R8: 10k; R0805
S2: SWITCH-SPDT-SMD-RIGHT-ANGLE; SWITCH_SPST_SMD_A
TCA9448A: MICROBUILDER_TCA9548A; MICROBUILDER_TSSOP24
U1: MIC5225-1.8V; SOT23-5
U$2: 243.5; 2*4*3.5
U$3, U$6, U$8, U$9, U$10, U$12: M0.9-HOLE0.9MM; M0.9-HOLE
U$13: FPC090505; FPC0905
U$21: MPU-9250_ICM20948; QFN24_3MM_NOEP

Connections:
1.8V: C2.1, C4.1, Q2.5 (G), Q3.2 (G), Q3.5 (G), R2.8 (2), R3.4 (1), R3.8 (2), U1.5 (OUT), U$13.P$7, U$21.8 (VDDIO), U$21.13 (VDD)
BATTERY: S2.2, U$10.P$1
BUTTON: U$2.P$4 (2), U$9.P$1
GND: C1.2, C2.2, C3.2, C4.2, C8.2, J1.1 (-), R4.2, R5.2, R6.2, S2.3 (S), TCA9448A.12 (GND), U1.2 (GND), U$2.P$3 (1), U$8.P$1, U$13.P$9, U$21.18 (GND), U$21.20 (GND)
unnamed: R5.1, TCA9448A.21 (A2)
unnamed: J1.2 (+), S2.1 (O)
unnamed: R4.1, TCA9448A.2 (A1)
unnamed: R6.1, TCA9448A.1 (A0)
REGOUT: C8.1, U$21.10 (REGOUT)
RESET: R8.1, TCA9448A.3 (#RESET)
SCK/SCL: Q3.3 (D), R3.6 (2), TCA9448A.5 (SCL0), U$13.P$6
SCK/SCL_1.8V: Q3.4 (S), R3.1, U$21.23 (SCL/SCLK)
SCL: TCA9448A.22 (SCL), U$12.P$1
SCL1: TCA9448A.7 (SCL1), U$13.P$4
SCL2: TCA9448A.9 (SCL2), U$13.P$2
SDA: TCA9448A.23 (SDA), U$6.P$1
SDA1: TCA9448A.6 (SDA1), U$13.P$3
SDA2: TCA9448A.8 (SDA2), U$13.P$1
SDI/SDA: Q3.6 (D), R3.7 (2), TCA9448A.4 (SDA0), U$13.P$5
SDI/SDA_1.8V: Q3.1 (S), R3.5 (2), U$21.24 (SDA/SDI)
SDO/ADR: Q2.3 (D), R2.2 (1)
SDO/ADR_1.8V: Q2.4 (S), R2.1, U$21.9 (AD0/SDO)
VIN: C1.1, C3.1, R2.7 (2), R3.2 (1), R3.3 (1), R8.2, TCA9448A.24 (VCC), U1.1 (IN), U1.3 (EN), U$3.P$1, U$13.P$8

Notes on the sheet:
I2C Pullups & Shift
STEMMA/I2C Headers
Power supply

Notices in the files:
parts and their libraries:
microbuilder: This work is placed in the public domain, and may be freely used for commercial and non-commercial work with the following conditions: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
SparkFun-Connectors: Licensing: Creative Commons ShareAlike 4.0 International - https://creativecommons.org/licenses/by-sa/4.0
